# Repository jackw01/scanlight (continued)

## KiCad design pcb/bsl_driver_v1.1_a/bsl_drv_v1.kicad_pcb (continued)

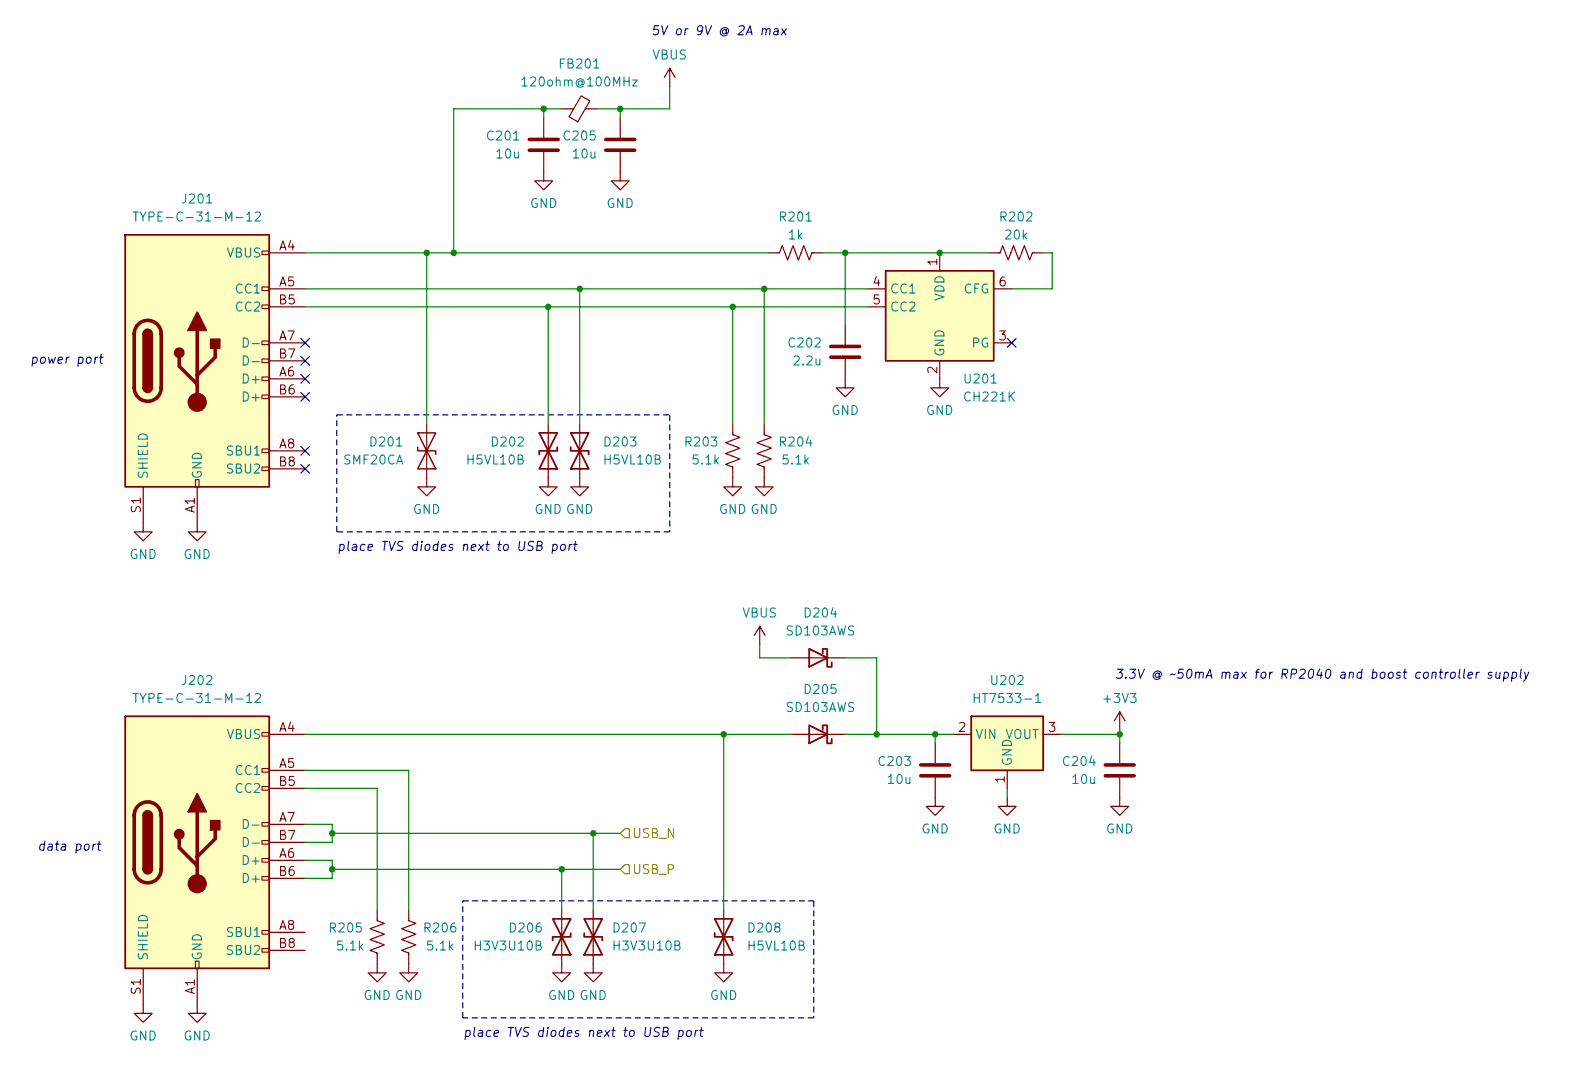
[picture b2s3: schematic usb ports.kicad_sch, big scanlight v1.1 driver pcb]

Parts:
C201, C203, C204, C205: 10u; C_0805_2012Metric; MPN CL21A106KAYNNNE; LCSC C15850
C202: 2.2u; C_0402_1005Metric; MPN CL05A225MQ5NSNC; LCSC C12530
D201: SMF20CA; D_SOD-123F; MPN SMF20CA; LCSC C42371747
D202, D203, D208: H5VL10B; D_SOD-882; MPN H5VL10B; LCSC C7420372
D204, D205: SD103AWS; D_SOD-323; MPN SD103AWS; LCSC C7420360
D206, D207: H3V3U10B; D_SOD-882; MPN H3V3U10B; LCSC C20615782
FB201: 120ohm@100MHz; L_0805_2012Metric; MPN UPZ2012E121-4R0TF; LCSC C97001
J201, J202: TYPE-C-31-M-12; USB_C_Receptacle_HRO_TYPE-C-31-M-12; MPN TYPE-C-31-M-12; LCSC C165948
R201: 1k; R_0402_1005Metric; MPN 0402WGF1001TCE; LCSC C11702
R202: 20k; R_0402_1005Metric; MPN 0402WGF2002TCE; LCSC C25765
R203, R204, R205, R206: 5.1k; R_0402_1005Metric; MPN 0402WGF5101TCE; LCSC C25905
U201: CH221K; SOT-23-6; MPN CH221K; LCSC C5125736
U202: HT7533-1; SOT-89-3; MPN HT7533-1; LCSC C14289

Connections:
+3V3: C204.1, U202.3 (VOUT); also elsewhere on the board
/usb ports/USB_N: D207.2 (A2), J202.A7 (D-), J202.B7 (D-); also elsewhere on the board
/usb ports/USB_P: D206.2 (A2), J202.A6 (D+), J202.B6 (D+); also elsewhere on the board
GND: C201.2, C202.2, C203.2, C204.2, C205.2, D201.1 (A1), D202.1 (A1), D203.1 (A1), D206.1 (A1), D207.1 (A1), D208.1 (A1), J201.A1 (GND), J201.A12 (GND), J201.B1 (GND), J201.B12 (GND), J201.S1 (SHIELD), J202.A1 (GND), J202.A12 (GND), J202.B1 (GND), J202.B12 (GND), J202.S1 (SHIELD), R203.1, R204.2, R205.1, R206.2, U201.2 (GND), U202.1 (GND); also elsewhere on the board
unnamed: C201.1, D201.2 (A2), FB201.1, J201.A4 (VBUS), J201.A9 (VBUS), J201.B4 (VBUS), J201.B9 (VBUS), R201.2
unnamed: D202.2 (A2), J201.B5 (CC2), R203.2, U201.5 (CC2)
unnamed: D203.2 (A2), J201.A5 (CC1), R204.1, U201.4 (CC1)
unnamed: C203.1, D204.1 (K), D205.1 (K), U202.2 (VIN)
unnamed: D205.2 (A), D208.2 (A2), J202.A4 (VBUS), J202.A9 (VBUS), J202.B4 (VBUS), J202.B9 (VBUS)
unnamed: J202.A5 (CC1), R206.1
unnamed: J202.B5 (CC2), R205.2
unnamed: R202.1, U201.6 (CFG)
unnamed: C202.1, R201.1, R202.2, U201.1 (VDD)
VBUS: C205.1, D204.2 (A), FB201.2; also elsewhere on the board

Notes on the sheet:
place TVS diodes next to USB port
power port
5V or 9V @ 2A max
3.3V @ ~50mA max for RP2040 and boost controller supply
data port

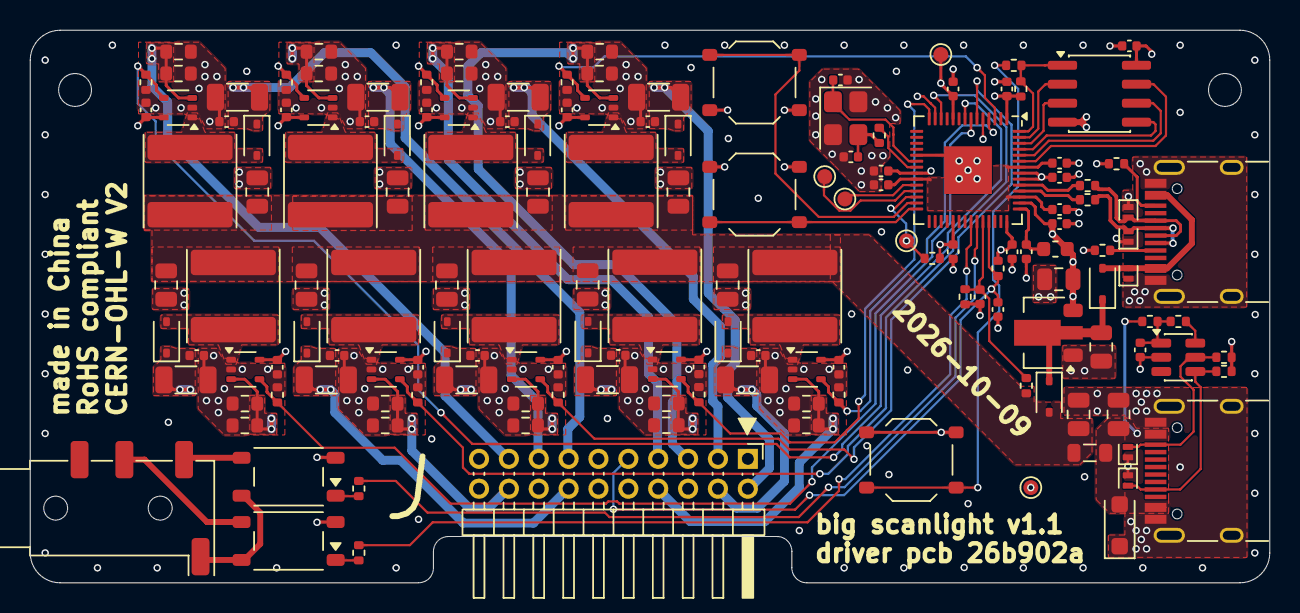
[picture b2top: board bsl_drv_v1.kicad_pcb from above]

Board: 4 copper layers, 83.0 x 37.0 mm, 159 parts (0 on the bottom side), 78 nets.

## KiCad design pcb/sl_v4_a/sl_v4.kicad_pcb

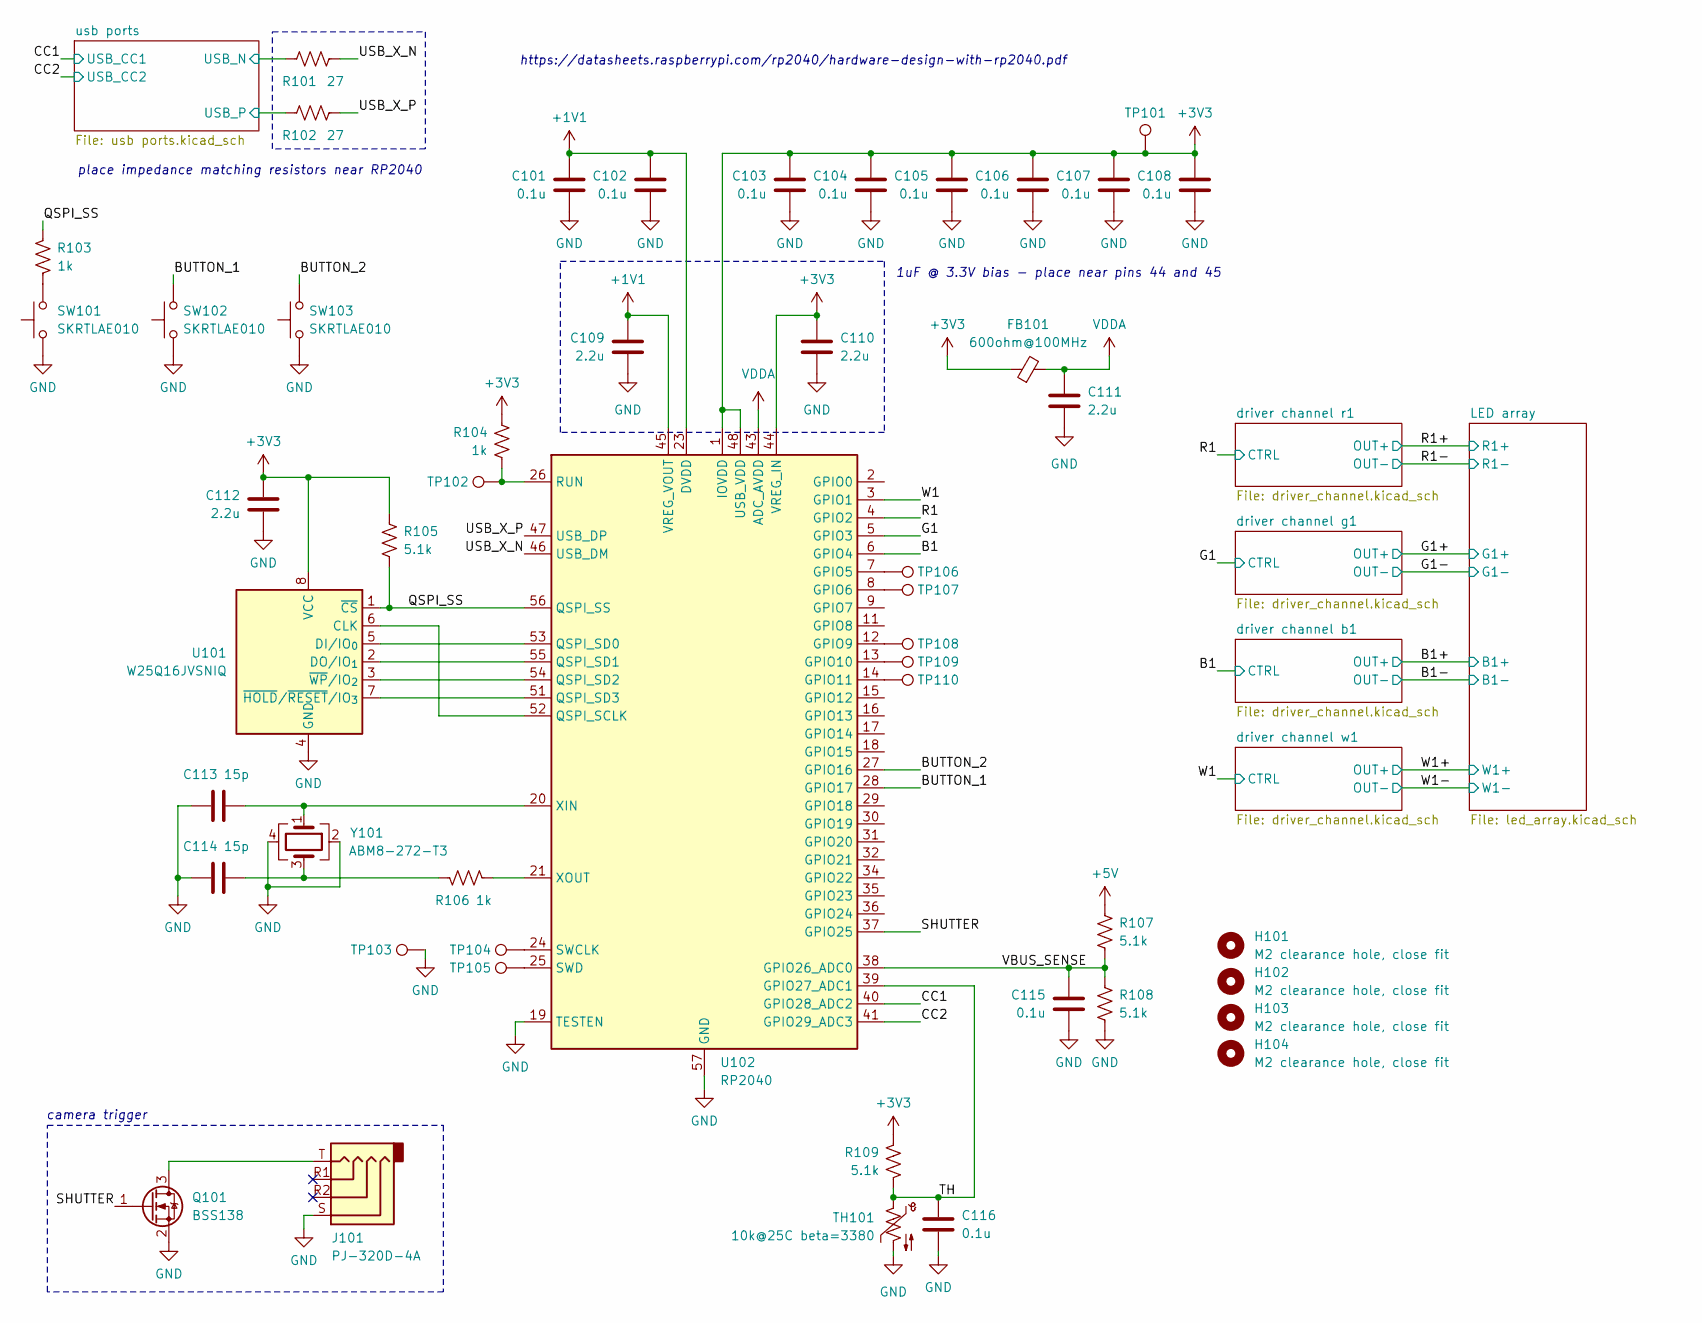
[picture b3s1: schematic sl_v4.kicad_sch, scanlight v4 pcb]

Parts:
C101, C102, C103, C104, C105, C106, C107, C108, C115, C116: 0.1u; C_0402_1005Metric; MPN CL05B104KB54PNC; LCSC C307331
C109, C110, C111, C112: 2.2u; C_0402_1005Metric; MPN CL05A225MQ5NSNC; LCSC C12530
C113, C114: 15p; C_0402_1005Metric; MPN 0402CG150J500NT; LCSC C1548
FB101: 600ohm@100MHz; L_0603_1608Metric; MPN GZ1608D601TF; LCSC C1002
H101, H102, H103, H104: M2 clearance hole, close fit; MountingHole_2.2mm_M2_Mask_tight
J101: PJ-320D-4A; Jack_3.5mm_KoreanHropartsElec_PJ-320D-4A_Horizontal; MPN PJ-320D-4A; LCSC C95562
Q101: BSS138; SOT-323_SC-70; MPN BSS138W; LCSC C28646265
R101, R102: 27; R_0402_1005Metric; MPN 0402WGF270JTCE; LCSC C25100
R103, R104, R106: 1k; R_0402_1005Metric; MPN 0402WGF1001TCE; LCSC C11702
R105, R107, R108, R109: 5.1k; R_0402_1005Metric; MPN 0402WGF5101TCE; LCSC C25905
SW101, SW102, SW103: SKRTLAE010; SW_Push_1P1T-MP_NO_Horizontal_Alps_SKRTLAE010; MPN SKRTLAE010; LCSC C110293
TH101: 10k@25C beta=3380; R_0603_1608Metric; MPN NCP18XH103F03RB; LCSC C13564
TP101, TP102, TP103, TP104, TP105, TP106, TP107, TP108, TP109, TP110: TestPoint; TestPoint_Pad_D1.0mm
U101: W25Q16JVSNIQ; SOIC-8_3.9x4.9mm_P1.27mm; MPN W25Q16JVSNIQ; LCSC C2456211
U102: RP2040; QFN-56-1EP_7x7mm_P0.4mm_EP3.2x3.2mm; MPN RP2040; LCSC C2040
Y101: ABM8-272-T3; Crystal_SMD_Abracon_ABM8G-4Pin_3.2x2.5mm; MPN ABM8-272-T3; LCSC C20625731

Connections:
+1V1: C101.1, C102.1, C109.1, U102.23 (DVDD), U102.45 (VREG_VOUT), U102.50 (DVDD)
+3V3: C103.1, C104.1, C105.1, C106.1, C107.1, C108.1, C110.1, C112.1, FB101.1, R104.2, R105.1, R109.1, TP101.1 (1_1), U101.8 (VCC), U102.1 (IOVDD), U102.10 (IOVDD), U102.22 (IOVDD), U102.33 (IOVDD), U102.42 (IOVDD), U102.44 (VREG_IN), U102.48 (USB_VDD), U102.49 (IOVDD); also elsewhere on the board
+5V: R107.2; also elsewhere on the board
/B1: U102.6 (GPIO4); also elsewhere on the board
/BUTTON_1: SW102.2, U102.28 (GPIO17)
/BUTTON_2: SW103.2, U102.27 (GPIO16)
/CC1: U102.40 (GPIO28_ADC2); also elsewhere on the board
/CC2: U102.41 (GPIO29_ADC3); also elsewhere on the board
/G1: U102.5 (GPIO3); also elsewhere on the board
/QSPI_SS: R103.2, R105.2, U101.1 (~CS), U102.56 (QSPI_SS)
/R1: U102.4 (GPIO2); also elsewhere on the board
/SHUTTER: Q101.1 (G), U102.37 (GPIO25)
/TH: C116.1, R109.2, TH101.1, U102.39 (GPIO27_ADC1)
/USB_X_N: R101.1, U102.46 (USB_DM)
/USB_X_P: R102.2, U102.47 (USB_DP)
/VBUS_SENSE: C115.1, R107.1, R108.1, U102.38 (GPIO26_ADC0)
/W1: U102.3 (GPIO1); also elsewhere on the board
/usb ports/USB_N: R101.2; also elsewhere on the board
/usb ports/USB_P: R102.1; also elsewhere on the board
GND: C101.2, C102.2, C103.2, C104.2, C105.2, C106.2, C107.2, C108.2, C109.2, C110.2, C111.2, C112.2, C113.1, C114.1, C115.2, C116.2, J101.S, Q101.2 (S), R108.2, SW101.1, SW102.1, SW103.1, TH101.2, TP103.1 (1_1), U101.4 (GND), U102.19 (TESTEN), U102.57 (GND), Y101.2, Y101.4; also elsewhere on the board
unnamed: C114.2, R106.1, Y101.3
unnamed: J101.T, Q101.3 (D)
unnamed: R103.1, SW101.2
unnamed: U101.6 (CLK), U102.52 (QSPI_SCLK)
unnamed: U101.5 (DI/IO_{0}), U102.53 (QSPI_SD0)
unnamed: U101.2 (DO/IO_{1}), U102.55 (QSPI_SD1)
unnamed: U101.7 (~HOLD/~RESET/IO_{3}), U102.51 (QSPI_SD3)
unnamed: U101.3 (~WP/IO_{2}), U102.54 (QSPI_SD2)
unnamed: TP106.1 (1_1), U102.7 (GPIO5)
unnamed: TP107.1 (1_1), U102.8 (GPIO6)
unnamed: TP108.1 (1_1), U102.12 (GPIO9)
unnamed: TP109.1 (1_1), U102.13 (GPIO10)
unnamed: TP110.1 (1_1), U102.14 (GPIO11)
unnamed: R104.1, TP102.1 (1_1), U102.26 (RUN)
unnamed: TP104.1 (1_1), U102.24 (SWCLK)
unnamed: TP105.1 (1_1), U102.25 (SWD)
unnamed: C113.2, U102.20 (XIN), Y101.1
unnamed: R106.2, U102.21 (XOUT)
VDDA: C111.1, FB101.2, U102.43 (ADC_AVDD)

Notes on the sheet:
place impedance matching resistors near RP2040
1uF @ 3.3V bias - place near pins 44 and 45
camera trigger
https://datasheets.raspberrypi.com/rp2040/hardware-design-with-rp2040.pdf

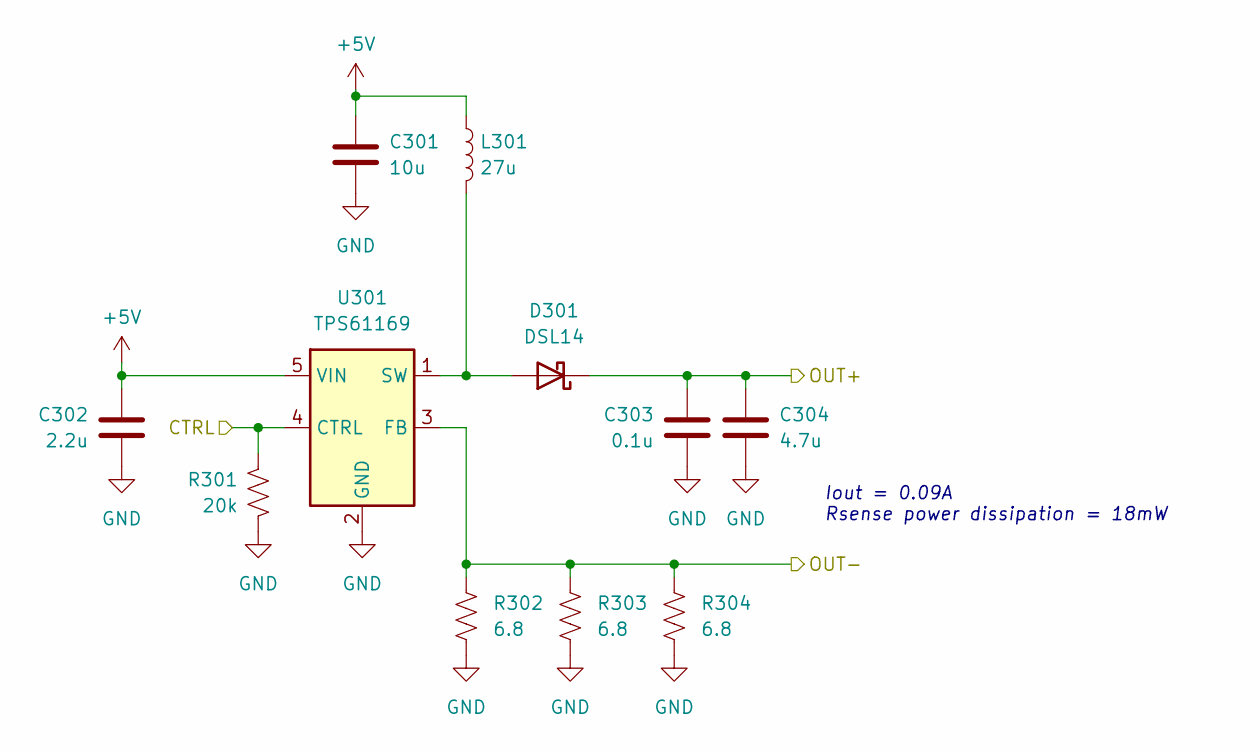
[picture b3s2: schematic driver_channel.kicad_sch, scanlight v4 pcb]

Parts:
C301: 10u; C_0805_2012Metric; MPN CL21A106KAYNNNE; LCSC C15850
C302: 2.2u; C_0402_1005Metric; MPN CL05A225MQ5NSNC; LCSC C12530
C303: 0.1u; C_0402_1005Metric; MPN CL05B104KB54PNC; LCSC C307331
C304: 4.7u; C_1206_3216Metric; MPN 1206B475K500NT; LCSC C29823
D301: DSL14; D_SOD-123F; MPN DSL14; LCSC C22466349
L301: 27u; L_Sunlord_SWPA6028S; MPN CR6028-270M; LCSC C7588756
R301: 20k; R_0402_1005Metric; MPN 0402WGF2002TCE; LCSC C25765
R302, R303, R304: 6.8; R_0402_1005Metric; MPN AC0402FR-076R8L; LCSC C227211
U301: TPS61169; SOT-353_SC-70-5; MPN TPS61169DCKR; LCSC C71045

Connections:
+5V: C301.1, C302.1, L301.1, U301.5 (VIN); also elsewhere on the board
/R1: R301.1, U301.4 (CTRL); also elsewhere on the board
/R1+: C303.1, C304.1, D301.1 (K); also elsewhere on the board
/R1-: R302.1, R303.1, R304.1, U301.3 (FB); also elsewhere on the board
GND: C301.2, C302.2, C303.2, C304.2, R301.2, R302.2, R303.2, R304.2, U301.2 (GND); also elsewhere on the board
unnamed: D301.2 (A), L301.2, U301.1 (SW)

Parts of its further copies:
C401, C501, C601: 10u; C_0805_2012Metric; MPN CL21A106KAYNNNE; LCSC C15850
C402, C502, C602: 2.2u; C_0402_1005Metric; MPN CL05A225MQ5NSNC; LCSC C12530
C403, C503, C603: 0.1u; C_0402_1005Metric; MPN CL05B104KB54PNC; LCSC C307331
C404, C504, C604: 4.7u; C_1206_3216Metric; MPN 1206B475K500NT; LCSC C29823
D401, D501, D601: DSL14; D_SOD-123F; MPN DSL14; LCSC C22466349
L401, L501, L601: 27u; L_Sunlord_SWPA6028S; MPN CR6028-270M; LCSC C7588756
R401, R501, R601: 20k; R_0402_1005Metric; MPN 0402WGF2002TCE; LCSC C25765
R402, R403, R404, R502, R503, R504, R602, R603, R604: 6.8; R_0402_1005Metric; MPN AC0402FR-076R8L; LCSC C227211
U401, U501, U601: TPS61169; SOT-353_SC-70-5; MPN TPS61169DCKR; LCSC C71045

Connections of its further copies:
+5V: C401.1, C402.1, C501.1, C502.1, C601.1, C602.1, L401.1, L501.1, L601.1, U401.5 (VIN), U501.5 (VIN), U601.5 (VIN); also elsewhere on the board
/B1: R501.1, U501.4 (CTRL); also elsewhere on the board
/B1+: C503.1, C504.1, D501.1 (K); also elsewhere on the board
/B1-: R502.1, R503.1, R504.1, U501.3 (FB); also elsewhere on the board
/G1: R401.1, U401.4 (CTRL); also elsewhere on the board
/G1+: C403.1, C404.1, D401.1 (K); also elsewhere on the board
/G1-: R402.1, R403.1, R404.1, U401.3 (FB); also elsewhere on the board
/W1: R601.1, U601.4 (CTRL); also elsewhere on the board
/W1+: C603.1, C604.1, D601.1 (K); also elsewhere on the board
/W1-: R602.1, R603.1, R604.1, U601.3 (FB); also elsewhere on the board
GND: C401.2, C402.2, C403.2, C404.2, C501.2, C502.2, C503.2, C504.2, C601.2, C602.2, C603.2, C604.2, R401.2, R402.2, R403.2, R404.2, R501.2, R502.2, R503.2, R504.2, R601.2, R602.2, R603.2, R604.2, U401.2 (GND), U501.2 (GND), U601.2 (GND); also elsewhere on the board
unnamed: D401.2 (A), L401.2, U401.1 (SW)
unnamed: D501.2 (A), L501.2, U501.1 (SW)
unnamed: D601.2 (A), L601.2, U601.1 (SW)

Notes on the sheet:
Iout = 0.09A Rsense power dissipation = 18mW

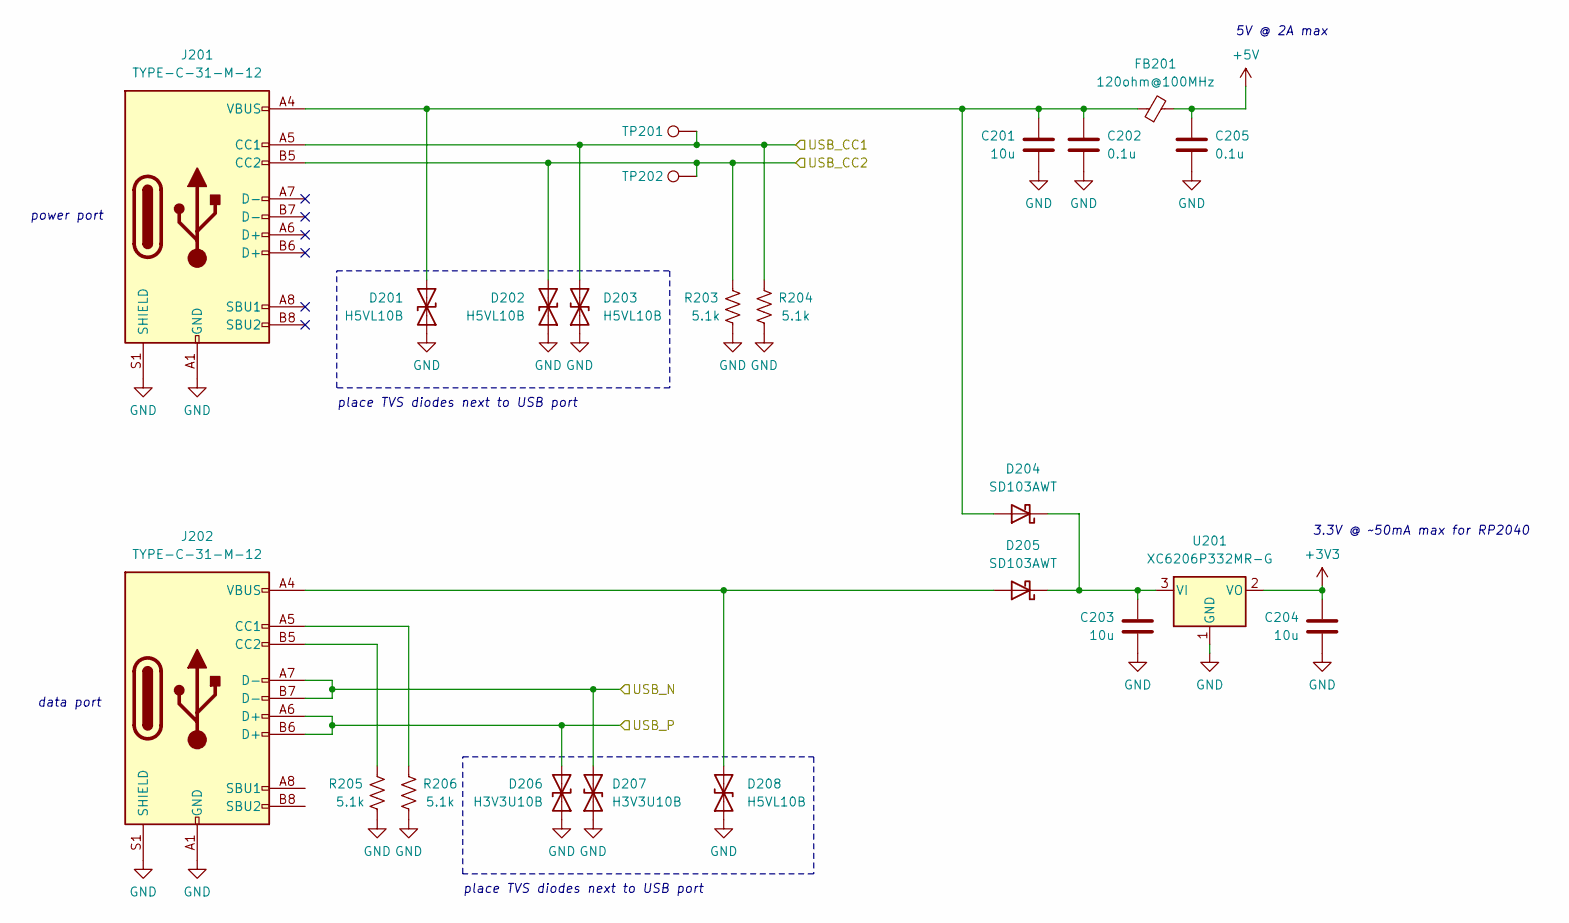
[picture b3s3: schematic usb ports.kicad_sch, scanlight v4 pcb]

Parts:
C201, C203, C204: 10u; C_0805_2012Metric; MPN CL21A106KAYNNNE; LCSC C15850
C202, C205: 0.1u; C_0402_1005Metric; MPN CL05B104KB54PNC; LCSC C307331
D201, D202, D203, D208: H5VL10B; D_SOD-882; MPN H5VL10B; LCSC C7420372
D204, D205: SD103AWT; D_SOD-523; MPN SD103AWT; LCSC C22466357
D206, D207: H3V3U10B; D_SOD-882; MPN H3V3U10B; LCSC C20615782
FB201: 120ohm@100MHz; L_0805_2012Metric; MPN UPZ2012E121-4R0TF; LCSC C97001
J201, J202: TYPE-C-31-M-12; USB_C_Receptacle_HRO_TYPE-C-31-M-12; MPN TYPE-C-31-M-12; LCSC C165948
R203, R204, R205, R206: 5.1k; R_0402_1005Metric; MPN 0402WGF5101TCE; LCSC C25905
TP201, TP202: TestPoint; TestPoint_Pad_D1.0mm
U201: XC6206P332MR-G; SOT-23-3; MPN XC6206P332MR-G; LCSC C5446

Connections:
+3V3: C204.1, U201.2 (VO); also elsewhere on the board
+5V: C205.1, FB201.2; also elsewhere on the board
/CC1: D203.2 (A2), J201.A5 (CC1), R204.1, TP201.1 (1_1); also elsewhere on the board
/CC2: D202.2 (A2), J201.B5 (CC2), R203.2, TP202.1 (1_1); also elsewhere on the board
/usb ports/USB_N: D207.2 (A2), J202.A7 (D-), J202.B7 (D-); also elsewhere on the board
/usb ports/USB_P: D206.2 (A2), J202.A6 (D+), J202.B6 (D+); also elsewhere on the board
GND: C201.2, C202.2, C203.2, C204.2, C205.2, D201.1 (A1), D202.1 (A1), D203.1 (A1), D206.1 (A1), D207.1 (A1), D208.1 (A1), J201.A1 (GND), J201.A12 (GND), J201.B1 (GND), J201.B12 (GND), J201.S1 (SHIELD), J202.A1 (GND), J202.A12 (GND), J202.B1 (GND), J202.B12 (GND), J202.S1 (SHIELD), R203.1, R204.2, R205.1, R206.2, U201.1 (GND); also elsewhere on the board
unnamed: C201.1, C202.1, D201.2 (A2), D204.2 (A), FB201.1, J201.A4 (VBUS), J201.A9 (VBUS), J201.B4 (VBUS), J201.B9 (VBUS)
unnamed: C203.1, D204.1 (K), D205.1 (K), U201.3 (VI)
unnamed: D205.2 (A), D208.2 (A2), J202.A4 (VBUS), J202.A9 (VBUS), J202.B4 (VBUS), J202.B9 (VBUS)
unnamed: J202.A5 (CC1), R206.1
unnamed: J202.B5 (CC2), R205.2

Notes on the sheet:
place TVS diodes next to USB port
power port
5V @ 2A max
3.3V @ ~50mA max for RP2040
data port

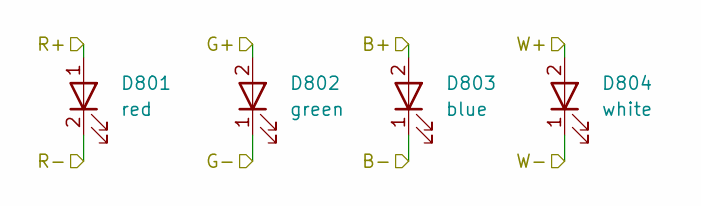
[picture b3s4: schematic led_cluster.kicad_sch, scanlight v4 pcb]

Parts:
D801: red; LED_2835_Reversed_Red_compact; MPN HL-AS-2835D15FC-S1-08-PCT-ZW-P6; LCSC C49435764
D802: green; LED_2835_compact; MPN TJ-S2835UG5W8TLC2G-A5; LCSC C440451
D803: blue; LED_2835_compact; MPN TJ-S2835UG5W8TLC6B-A5; LCSC C440452
D804: white; LED_2835_compact; MPN HL-AM-2835H421W-S1-08-HR6(SDCM<6)(4750K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; LCSC C516133

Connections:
/B1+: D803.2 (A); also elsewhere on the board
/G1+: D802.2 (A); also elsewhere on the board
/LED array/LED Cluster 0/B-: D803.1 (K); also elsewhere on the board
/LED array/LED Cluster 0/G-: D802.1 (K); also elsewhere on the board
/LED array/LED Cluster 0/R-: D801.2 (K); also elsewhere on the board
/LED array/LED Cluster 0/W-: D804.1 (K); also elsewhere on the board
/R1+: D801.1 (A); also elsewhere on the board
/W1+: D804.2 (A); also elsewhere on the board

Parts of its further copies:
D901, D1001, D1101, D1201, D1301, D1401, D1501, D1601: red; LED_2835_Reversed_Red_compact; MPN HL-AS-2835D15FC-S1-08-PCT-ZW-P6; LCSC C49435764
D902, D1002, D1102, D1202, D1302, D1402, D1502, D1602: green; LED_2835_compact; MPN TJ-S2835UG5W8TLC2G-A5; LCSC C440451
D903, D1003, D1103, D1203, D1303, D1403, D1503, D1603: blue; LED_2835_compact; MPN TJ-S2835UG5W8TLC6B-A5; LCSC C440452
D904, D1004, D1104, D1204, D1304, D1404, D1504, D1604: white; LED_2835_compact; MPN HL-AM-2835H421W-S1-08-HR6(SDCM<6)(4750K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; LCSC C516133

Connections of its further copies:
/B1-: D1603.1 (K); also elsewhere on the board
/G1-: D1602.1 (K); also elsewhere on the board
/LED array/LED Cluster 0/B-: D903.2 (A); also elsewhere on the board
/LED array/LED Cluster 0/G-: D902.2 (A); also elsewhere on the board
/LED array/LED Cluster 0/R-: D901.1 (A); also elsewhere on the board
/LED array/LED Cluster 0/W-: D904.2 (A); also elsewhere on the board
/LED array/LED Cluster 1/B-: D903.1 (K), D1003.2 (A)
/LED array/LED Cluster 1/G-: D902.1 (K), D1002.2 (A)
/LED array/LED Cluster 1/R-: D901.2 (K), D1001.1 (A)
/LED array/LED Cluster 1/W-: D904.1 (K), D1004.2 (A)
/LED array/LED Cluster 2/B-: D1003.1 (K), D1103.2 (A)
/LED array/LED Cluster 2/G-: D1002.1 (K), D1102.2 (A)
/LED array/LED Cluster 2/R-: D1001.2 (K), D1101.1 (A)
/LED array/LED Cluster 2/W-: D1004.1 (K), D1104.2 (A)
/LED array/LED Cluster 3/B-: D1103.1 (K), D1203.2 (A)
/LED array/LED Cluster 3/G-: D1102.1 (K), D1202.2 (A)
/LED array/LED Cluster 3/R-: D1101.2 (K), D1201.1 (A)
/LED array/LED Cluster 3/W-: D1104.1 (K), D1204.2 (A)
/LED array/LED Cluster 4/B-: D1203.1 (K), D1303.2 (A)
/LED array/LED Cluster 4/G-: D1202.1 (K), D1302.2 (A)
/LED array/LED Cluster 4/R-: D1201.2 (K), D1301.1 (A)
/LED array/LED Cluster 4/W-: D1204.1 (K), D1304.2 (A)
/LED array/LED Cluster 5/B-: D1303.1 (K), D1403.2 (A)
/LED array/LED Cluster 5/G-: D1302.1 (K), D1402.2 (A)
/LED array/LED Cluster 5/R-: D1301.2 (K), D1401.1 (A)
/LED array/LED Cluster 5/W-: D1304.1 (K), D1404.2 (A)
/LED array/LED Cluster 6/B-: D1403.1 (K), D1503.2 (A)
/LED array/LED Cluster 6/G-: D1402.1 (K), D1502.2 (A)
/LED array/LED Cluster 6/R-: D1401.2 (K), D1501.1 (A)
/LED array/LED Cluster 6/W-: D1404.1 (K), D1504.2 (A)
/LED array/LED Cluster 7/B-: D1503.1 (K), D1603.2 (A)
/LED array/LED Cluster 7/G-: D1502.1 (K), D1602.2 (A)
/LED array/LED Cluster 7/R-: D1501.2 (K), D1601.1 (A)
/LED array/LED Cluster 7/W-: D1504.1 (K), D1604.2 (A)
/R1-: D1601.2 (K); also elsewhere on the board
/W1-: D1604.1 (K); also elsewhere on the board

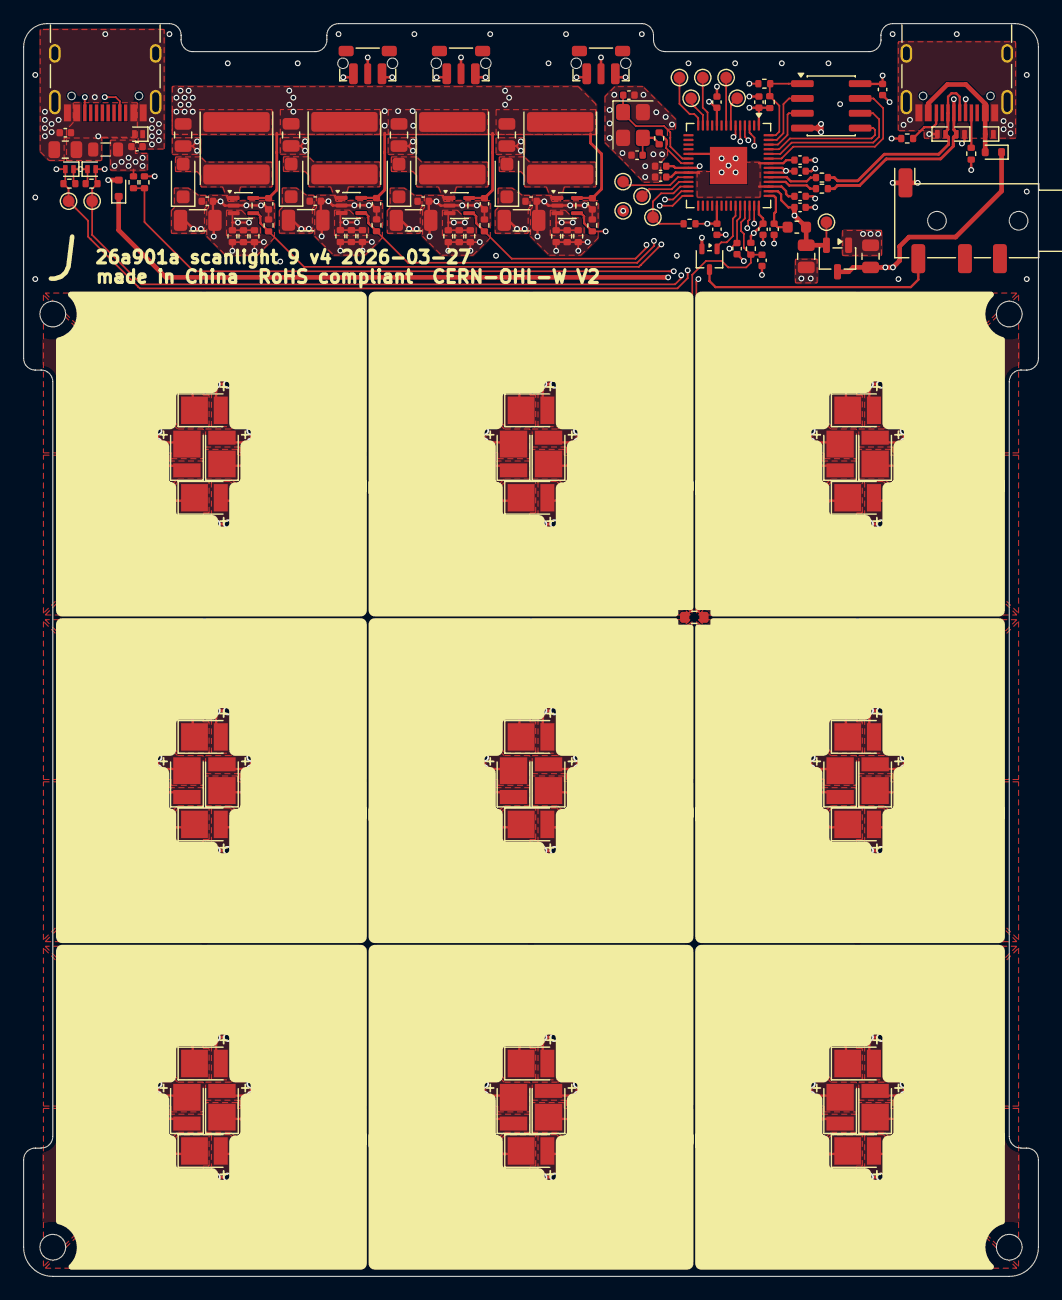
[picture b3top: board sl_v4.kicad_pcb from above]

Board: 4 copper layers, 87.0 x 107.4 mm, 152 parts (0 on the bottom side), 88 nets.

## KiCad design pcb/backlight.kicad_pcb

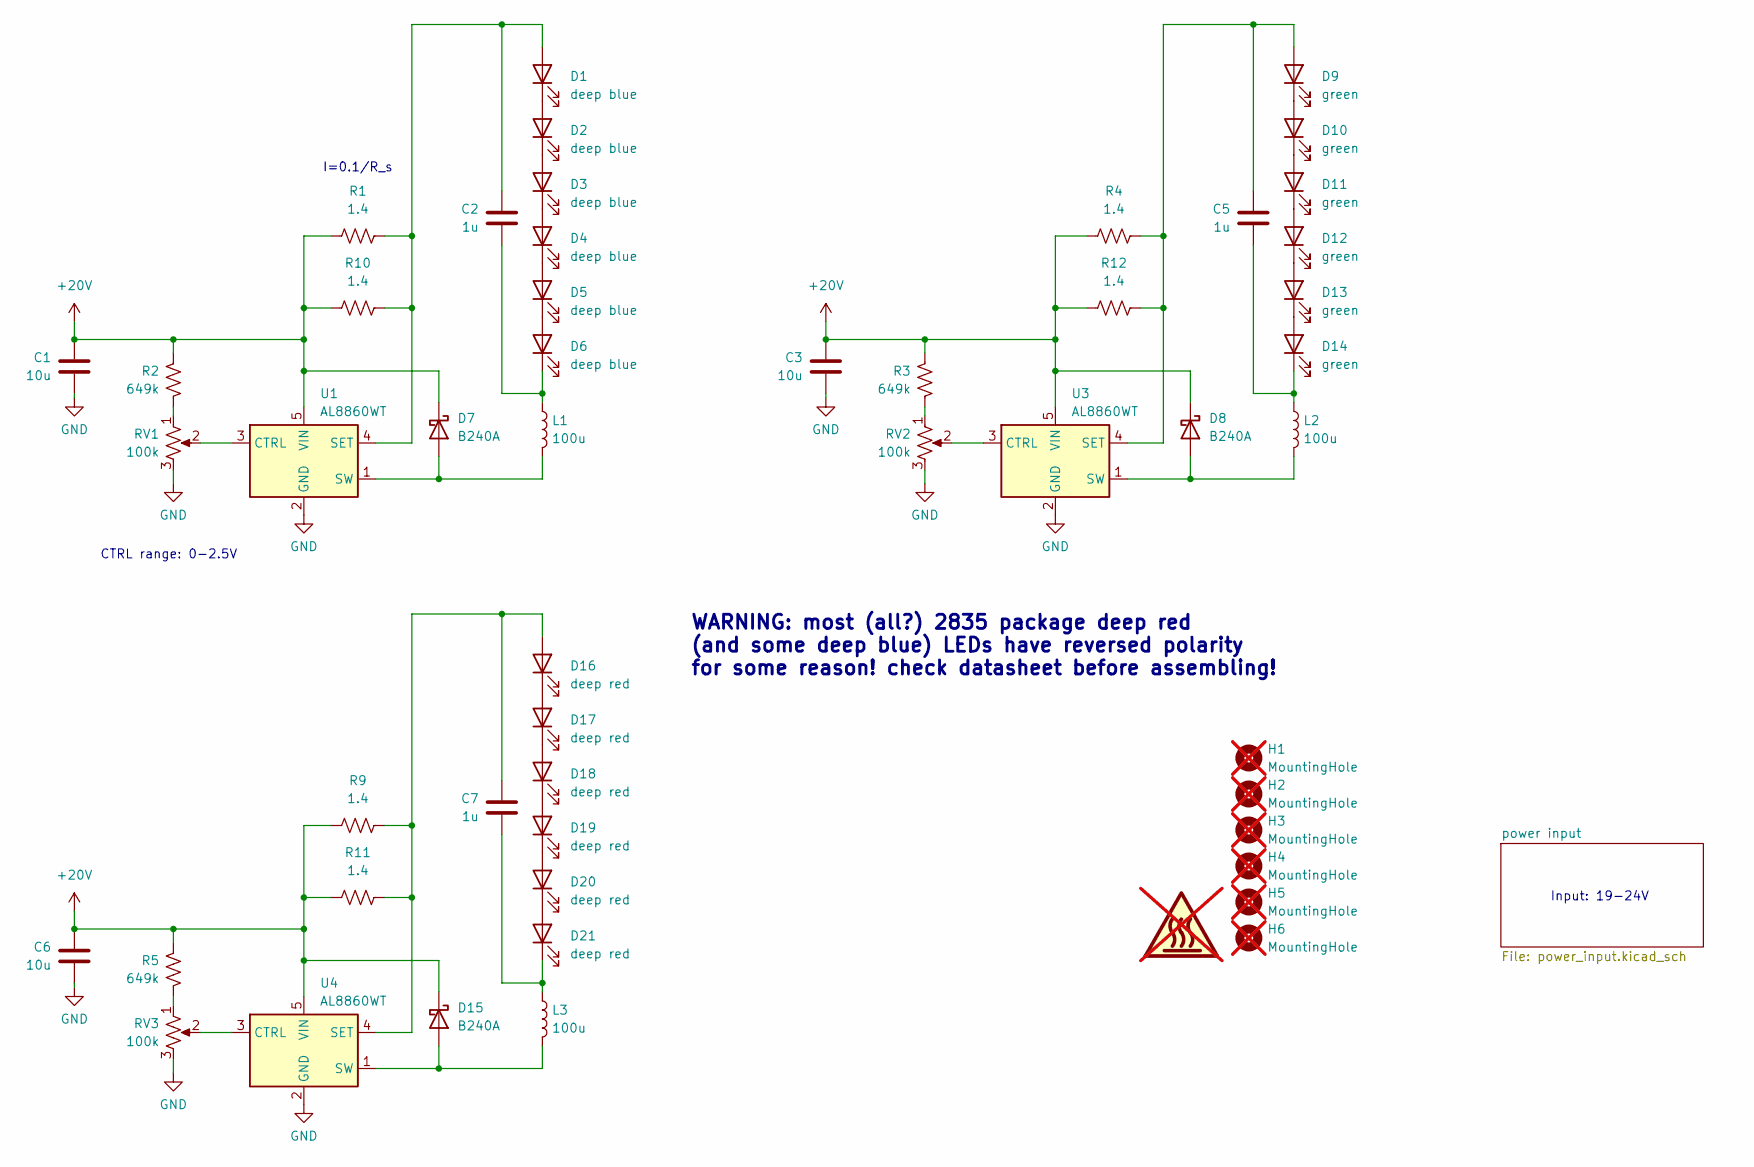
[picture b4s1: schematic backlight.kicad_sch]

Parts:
C1, C3, C6: 10u; C_1210_3225Metric; MPN Generic 10uF 50V 1210 X7R
C2, C5, C7: 1u; C_0603_1608Metric; MPN Generic 1uF 25V 0603 X7R
D1, D2, D3, D4, D5, D6: deep blue; LED_PLCC_2835_Handsoldering; MPN JE2835ARY-N-0002A0000-N0000001
D7, D8, D15: B240A; D_SMA; MPN B240A-13-F
D9, D10, D11, D12, D13, D14: green; LED_PLCC_2835_Handsoldering; MPN JE2835AGR-N-0002A0000-N0000001
D16, D17, D18, D19, D20, D21: deep red; LED_PLCC_2835_Handsoldering; MPN 67-21S/NDR3C-P5080C1C51827Z15/2T
H1, H2, H3, H4, H5, H6: MountingHole; MountingHole_2.2mm_M2_Mask_5mm; not fitted
L1, L2, L3: 100u; L_Bourns_SRN8040TA; MPN HPC 8040NV-101M
R1, R4, R9, R10, R11, R12: 1.4; R_1206_3216Metric; MPN RK73H2ATTD1R40F
R2, R3, R5: 649k; R_0603_1608Metric; MPN Generic 649KOhm 0603 1%
RV1, RV2, RV3: 100k; Potentiometer_Bourns_PTV09A-1_Single_Vertical; MPN PTV09A-4020U-B104
SYM101: SYM_Hot_Large; hot-surface_1x; not fitted
U1, U3, U4: AL8860WT; TSOT-23-5; MPN AL8860WT-7

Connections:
+20V: C1.1, C3.1, C6.1, D7.1 (K), D8.1 (K), D15.1 (K), R1.1, R2.1, R3.1, R4.1, R5.1, R9.1, R10.1, R11.1, R12.1, U1.5 (VIN), U3.5 (VIN), U4.5 (VIN); also elsewhere on the board
GND: C1.2, C3.2, C6.2, RV1.3, RV2.3, RV3.3, U1.2 (GND), U3.2 (GND), U4.2 (GND); also elsewhere on the board
unnamed: C2.1, D1.2 (A), R1.2, R10.2, U1.4 (SET)
unnamed: D1.1 (K), D2.2 (A)
unnamed: D2.1 (K), D3.2 (A)
unnamed: D3.1 (K), D4.2 (A)
unnamed: D4.1 (K), D5.2 (A)
unnamed: D5.1 (K), D6.2 (A)
unnamed: C2.2, D6.1 (K), L1.1
unnamed: D7.2 (A), L1.2, U1.1 (SW)
unnamed: D8.2 (A), L2.2, U3.1 (SW)
unnamed: C5.1, D9.2 (A), R4.2, R12.2, U3.4 (SET)
unnamed: D9.1 (K), D10.2 (A)
unnamed: D10.1 (K), D11.2 (A)
unnamed: D11.1 (K), D12.2 (A)
unnamed: D12.1 (K), D13.2 (A)
unnamed: D13.1 (K), D14.2 (A)
unnamed: C5.2, D14.1 (K), L2.1
unnamed: D15.2 (A), L3.2, U4.1 (SW)
unnamed: C7.1, D16.1 (A), R9.2, R11.2, U4.4 (SET)
unnamed: D16.2 (K), D17.1 (A)
unnamed: D17.2 (K), D18.1 (A)
unnamed: D18.2 (K), D19.1 (A)
unnamed: D19.2 (K), D20.1 (A)
unnamed: D20.2 (K), D21.1 (A)
unnamed: C7.2, D21.2 (K), L3.1
unnamed: R2.2, RV1.1
unnamed: R3.2, RV2.1
unnamed: R5.2, RV3.1
unnamed: RV1.2, U1.3 (CTRL)
unnamed: RV2.2, U3.3 (CTRL)
unnamed: RV3.2, U4.3 (CTRL)

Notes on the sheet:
Input: 19-24V
CTRL range: 0-2.5V
I=0.1/R_s
WARNING: most (all?) 2835 package deep red (and some deep blue) LEDs have reversed polarity for some reason! check datasheet before assembling!

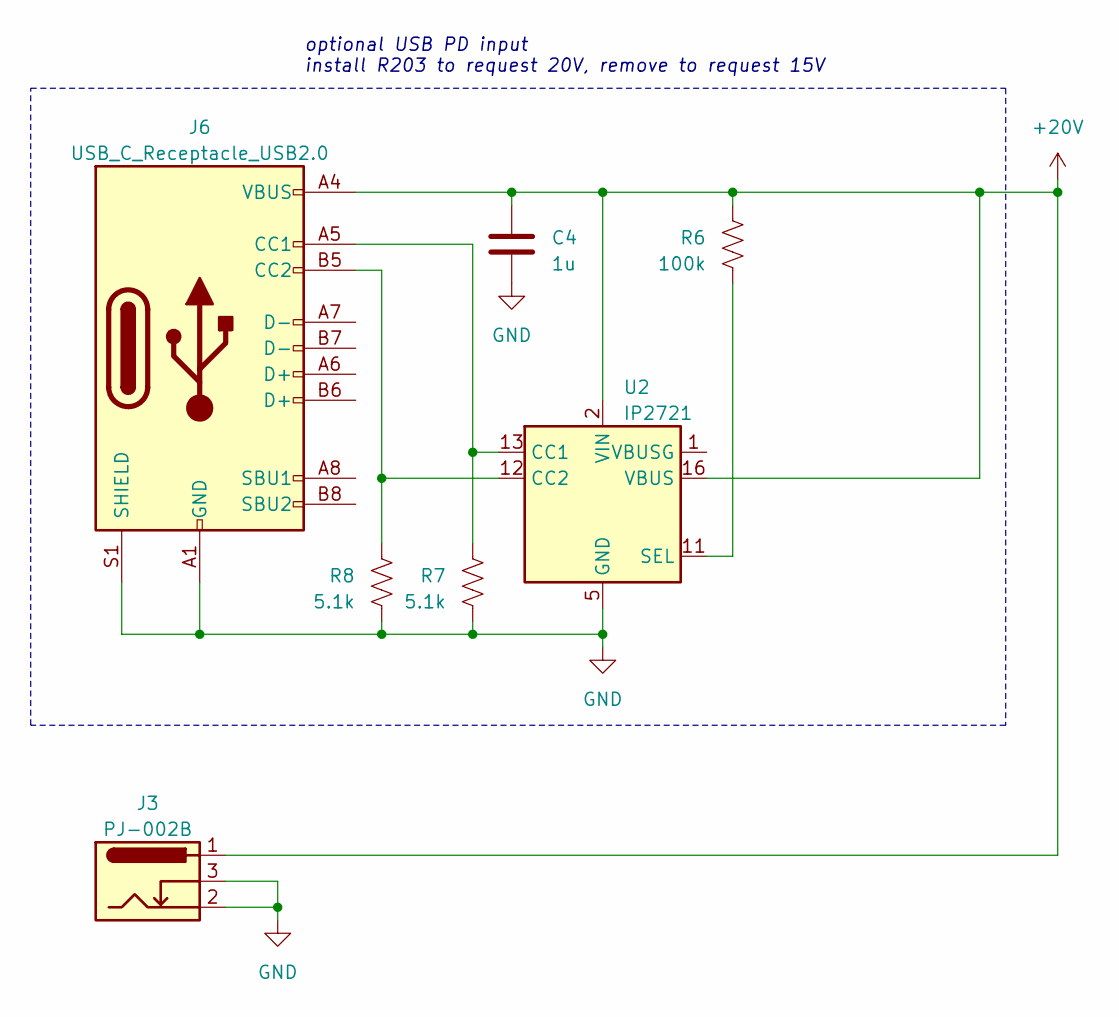
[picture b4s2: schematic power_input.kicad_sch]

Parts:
C4: 1u; C_0603_1608Metric; MPN Generic 1uF 25V 0603 X7R
J3: PJ-002B; BarrelJack_GCT_DCJ200-10-A_Horizontal; MPN PJ-002B
J6: USB_C_Receptacle_USB2.0; USB_C_Receptacle_GCT_USB4105-xx-A_16P_TopMnt_Horizontal; MPN USB4105-GF-A
R6: 100k; R_0603_1608Metric; MPN Generic 100KOhm 0603 5%
R7, R8: 5.1k; R_0603_1608Metric; MPN Generic 5.1KOhm 0603 5%
U2: IP2721; TSSOP-16_4.4x5mm_P0.65mm; MPN IP2721

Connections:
+20V: C4.2, J3.1, J6.A4 (VBUS), J6.A9 (VBUS), J6.B4 (VBUS), J6.B9 (VBUS), R6.1, U2.2 (VIN), U2.16 (VBUS); also elsewhere on the board
GND: C4.1, J3.2, J3.3, J6.A1 (GND), J6.A12 (GND), J6.B1 (GND), J6.B12 (GND), J6.S1 (SHIELD), R7.2, R8.2, U2.5 (GND); also elsewhere on the board
unnamed: J6.A5 (CC1), R7.1, U2.13 (CC1)
unnamed: J6.B5 (CC2), R8.1, U2.12 (CC2)
unnamed: R6.2, U2.11 (SEL)

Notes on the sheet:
optional USB PD input install R203 to request 20V, remove to request 15V
